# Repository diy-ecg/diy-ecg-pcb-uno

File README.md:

# diy-ecg-pcb-uno
 
# DIY ECG Amplifier Board (Arduino Uno Shield)

This repository contains the KiCad (v9) design files for a **DIY ECG (Electrocardiogram) amplifier board**.
The board is designed as an **Arduino Uno–compatible shield** and is intended for **educational, experimental, and research use**.

## Overview
- Analog front-end for ECG signal acquisition
- Designed for **Einthoven Lead I** measurements
- Uses a **MCP6004** quad operational amplifier
- Includes:
  - Differential ECG amplification
  - Biasing to a virtual ground (mid-supply)
  - Common-mode / body reference feedback (DRL-like concept)

The design is optimized for **low-cost components** and **didactic clarity**, making it suitable for
university courses, lab exercises, and DIY learning projects.

## Files
The repository intentionally contains only the essential KiCad files:
- `.kicad_sch` – schematic
- `.kicad_pcb` – PCB layout
- `.kicad_pro` – project file

These files are sufficient to inspect, modify, and manufacture the board.

## Intended Use
This board is **not a medical device** and must **not** be used for diagnostic or clinical purposes.
It is intended exclusively for:
- Education and teaching
- Private experimentation
- Research and prototyping

## License
This hardware design is licensed under the  
**CERN Open Hardware Licence Version 2 – Non-Commercial (CERN-OHL-NC v2)**.

You are free to study, modify, and manufacture the design for **private, educational, and research purposes**.
**Commercial use, sale, or mass production is not permitted** without explicit permission.

## Author
Jens Bongartz - info@diy-ecg.org

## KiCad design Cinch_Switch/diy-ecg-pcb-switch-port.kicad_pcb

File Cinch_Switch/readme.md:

These are KiCAD Files with switched TRRS connectors to fit Cinch adapters.

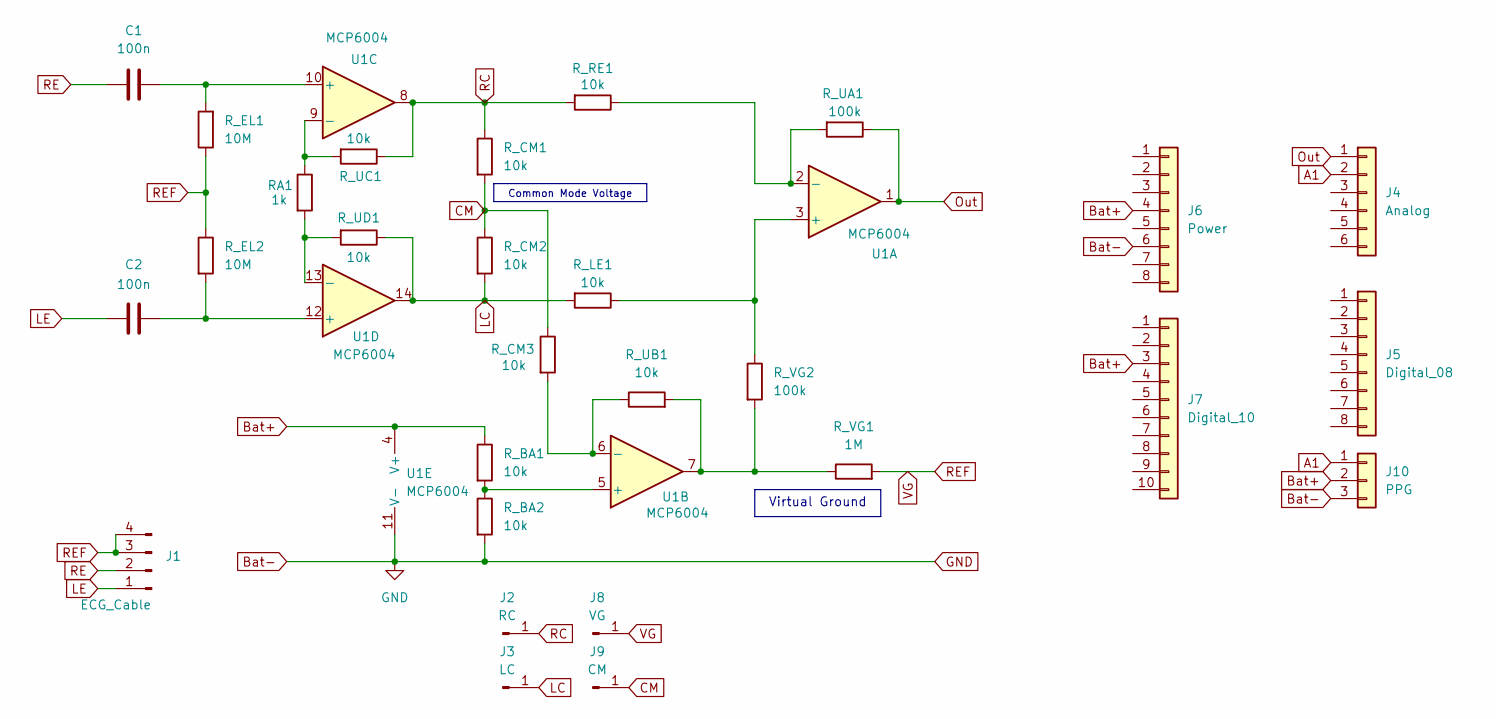
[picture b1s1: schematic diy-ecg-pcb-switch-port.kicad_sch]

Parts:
C1: 100n; C_Disc_D5.0mm_W2.5mm_P5.00mm
C2: 100n; C_Disc_D4.7mm_W2.5mm_P5.00mm
J1: ECG_Cable; PinHeader_1x04_P2.54mm_Vertical
J2: RC; PinHeader_1x01_P2.54mm_Vertical
J3: LC; PinHeader_1x01_P2.54mm_Vertical
J4: Analog; PinHeader_1x06_P2.54mm_Vertical
J5: Digital_08; PinHeader_1x08_P2.54mm_Vertical
J6: Power; PinHeader_1x08_P2.54mm_Vertical
J7: Digital_10; PinHeader_1x10_P2.54mm_Vertical
J8: VG; PinHeader_1x01_P2.54mm_Vertical
J9: CM; PinHeader_1x01_P2.54mm_Vertical
J10: PPG; PinHeader_1x03_P2.54mm_Horizontal
RA1: 1k; R_Axial_DIN0207_L6.3mm_D2.5mm_P10.16mm_Horizontal
R_BA1, R_BA2: 10k; R_Axial_DIN0207_L6.3mm_D2.5mm_P10.16mm_Horizontal
R_CM1, R_CM2, R_CM3: 10k; R_Axial_DIN0207_L6.3mm_D2.5mm_P10.16mm_Horizontal
R_EL1, R_EL2: 10M; R_Axial_DIN0207_L6.3mm_D2.5mm_P10.16mm_Horizontal
R_LE1: 10k; R_Axial_DIN0207_L6.3mm_D2.5mm_P10.16mm_Horizontal
R_RE1: 10k; R_Axial_DIN0207_L6.3mm_D2.5mm_P10.16mm_Horizontal
R_UA1: 100k; R_Axial_DIN0207_L6.3mm_D2.5mm_P10.16mm_Horizontal
R_UB1: 10k; R_Axial_DIN0207_L6.3mm_D2.5mm_P10.16mm_Horizontal
R_UC1: 10k; R_Axial_DIN0207_L6.3mm_D2.5mm_P10.16mm_Horizontal
R_UD1: 10k; R_Axial_DIN0207_L6.3mm_D2.5mm_P10.16mm_Horizontal
R_VG1: 1M; R_Axial_DIN0207_L6.3mm_D2.5mm_P10.16mm_Horizontal
R_VG2: 100k; R_Axial_DIN0207_L6.3mm_D2.5mm_P10.16mm_Horizontal
U1: MCP6004; DIP-14_W7.62mm_LongPads

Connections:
A1: J4.2 (A1), J10.1
Bat+: J6.4 (3V3), J7.3 (AREF), J10.2, R_BA1.1, U1.4 (V+)
Bat-: J6.6 (GND), J10.3, R_BA2.2, U1.11 (V-)
CM: J9.1, R_CM1.2, R_CM2.1, R_CM3.1
LC: J3.1, R_CM2.2, R_LE1.2, R_UD1.1, U1.14
LE: C2.2, J1.1
unnamed: R_UB1.2, R_VG1.1, R_VG2.2, U1.7
unnamed: R_LE1.1, R_VG2.1, U1.3 (+)
unnamed: R_RE1.1, R_UA1.2, U1.2 (-)
unnamed: R_BA1.2, R_BA2.1, U1.5 (+)
unnamed: R_CM3.2, R_UB1.1, U1.6 (-)
unnamed: C1.1, R_EL1.2, U1.10 (+)
unnamed: RA1.1, R_UC1.2, U1.9 (-)
unnamed: C2.1, R_EL2.2, U1.12 (+)
unnamed: RA1.2, R_UD1.2, U1.13 (-)
Out: J4.1 (A0), R_UA1.1, U1.1
RC: J2.1, R_CM1.1, R_RE1.2, R_UC1.1, U1.8
RE: C1.2, J1.2
REF: J1.3, J1.4, J8.1, R_EL1.1, R_EL2.1, R_VG1.2

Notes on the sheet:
Common Mode Voltage
Virtual Ground

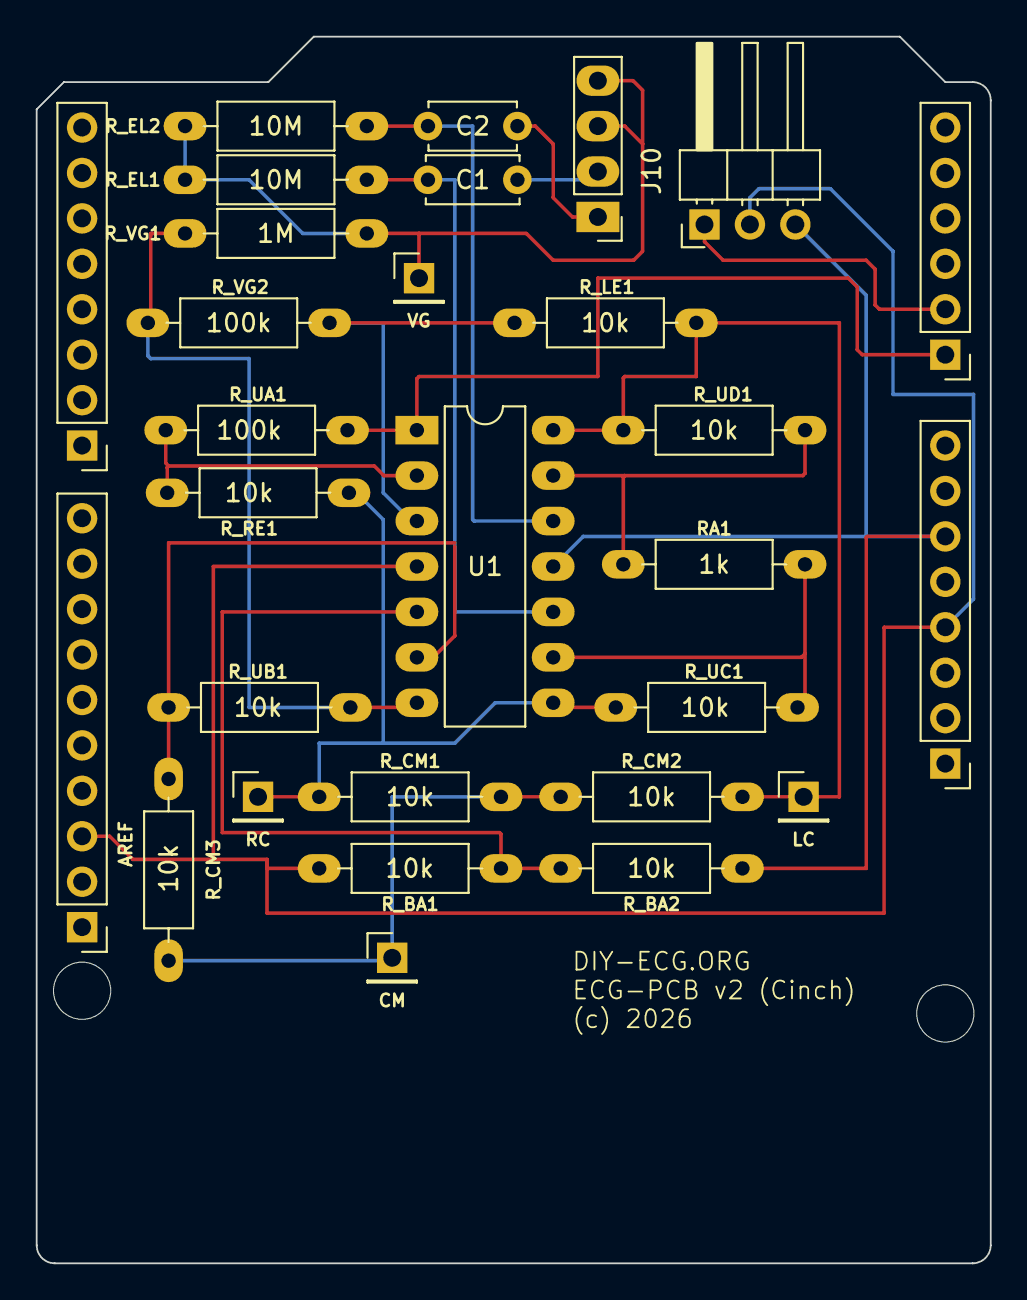
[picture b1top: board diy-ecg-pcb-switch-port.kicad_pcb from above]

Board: 2 copper layers, 53.3 x 68.6 mm, 31 parts (0 on the bottom side), 19 nets.

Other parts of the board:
H2: MountingHole2; Arduino_MountingHole
H4: MountingHole4; Arduino_MountingHole

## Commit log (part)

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2026-01-05 Initial Project Upload
2026-01-05 Initial Readme
    Added detailed project description, intended use, and licensing information.
2026-01-05 I
    Updated README to specify KiCad version and removed commercial license note.
2026-01-05 Fix formatting
    Removed an empty line at the beginning of the README.

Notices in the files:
Cinch_Switch/diy-ecg-pcb-switch-port.kicad_pcb:
(c) 2026
